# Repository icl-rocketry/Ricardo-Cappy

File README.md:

Hi. Welcome to the repo for Ricardo-Cappy.

Ricardo-Cappy is a custom HAT (Hardware Attached on Top) for the Raspberry Pi 5 to be used on the Payload lander for the 2026 ICLR launch.

It contains IMU sensors based on Ricardo-PickleRick, wirecutter modules, motor drivers for deploying landing legs, GPS and Radio capabilities as well as power systems for both the Raspberry Pi and the onboard components.

Contents:

-Hardware - contains the KiCad schematics and PCB layouts for Ricardo-Cappy, including symbols and footprints for parts not in the ICLR library. This is necessary for viewing and editing the KiCad files on your own device. 

To use the hardware files:
1. Install the ICLR symbol and footprint library (see their repo for detailed instructions, I forgot the link but you can use google)
2. Clone the repository onto your computer.
3. Install my custom libraries into KiCad (see instructions in KiCad documentation)

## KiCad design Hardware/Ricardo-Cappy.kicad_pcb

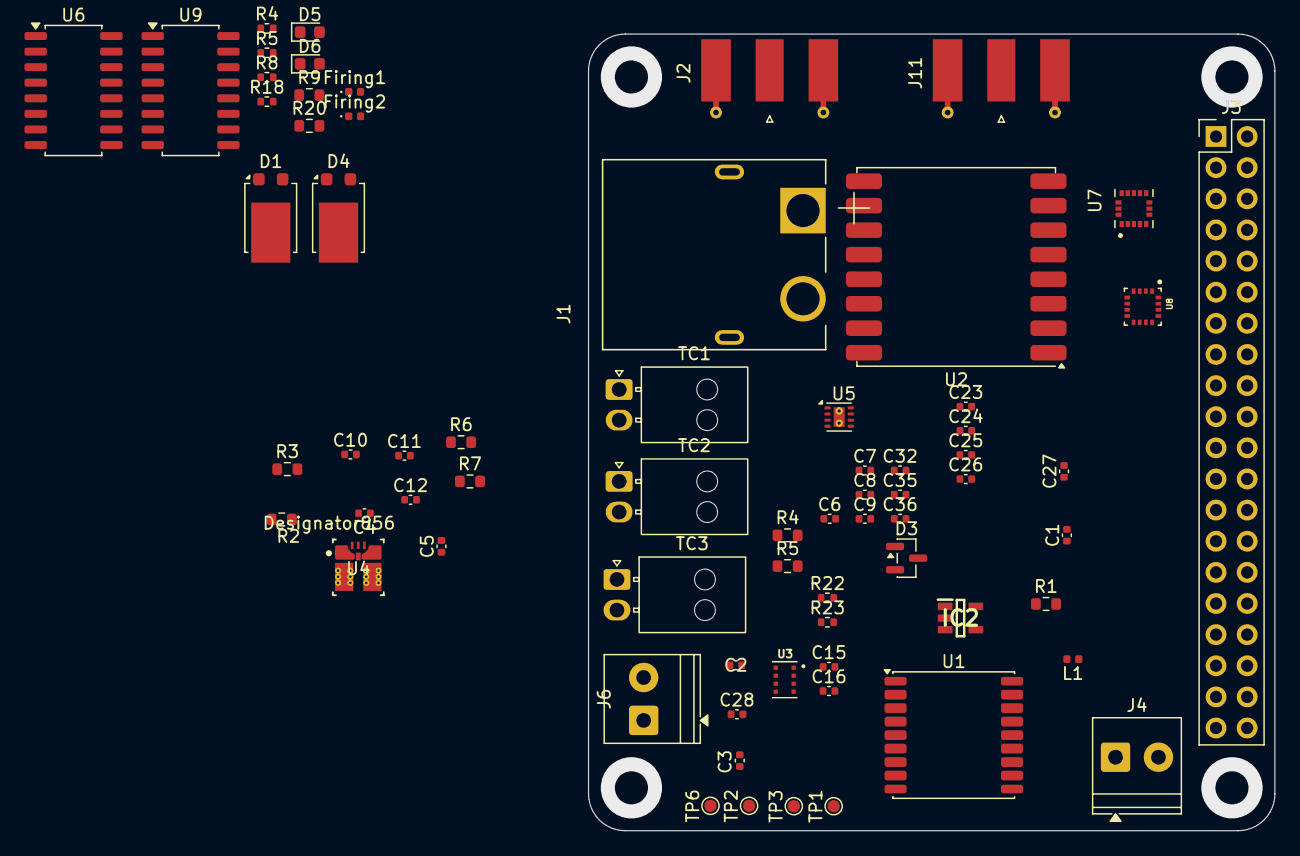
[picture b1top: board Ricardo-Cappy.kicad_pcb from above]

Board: 2 copper layers, 56.0 x 65.0 mm, 69 parts (0 on the bottom side), 47 nets, no tracks yet.

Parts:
C1, C6, C12, C24: 10nF; C_0402_1005Metric
C2, C10, C27, C35: 10uF; C_0402_1005Metric
C3, C11, C15, C16, C36: 100nF; C_0402_1005Metric
C4, C8: 10pF; C_0402_1005Metric
C5: 47uF; C_0402_1005Metric
C7: 47pF; C_0402_1005Metric
C9, C28: 1uF; C_0402_1005Metric
C23: 0.47uF; C_0402_1005Metric
C25: 0.1uF; C_0402_1005Metric
C26, C32: 2.2uF; C_0402_1005Metric
D1, D4: DST1550S; TO-277B
D3: MMBZ6V2ALT1G; SOT-23
D5, D6: RED_LED; LED_0603_1608Metric
Firing1, Firing2: EMERALD_LED; LED_0402_1005Metric
IC2: AP2205-W5-7; SOT95P282X145-5N
J1: XT60PW-M; AMASS_XT60PW-M
J2, J11: Conn_Coaxial; SMA_Molex_73251-1153_EdgeMount_Horizontal
J3: Conn_02x20_Odd_Even; PinHeader_2x20_P2.54mm_Vertical
J4, J6: Conn_01x02_Male; TerminalBlock_Phoenix_PT-1,5-2-3.5-H_1x02_P3.50mm_Horizontal
L1: 27nH; L_0402_1005Metric
R1: 10; R_0603_1608Metric
R2: 226K; R_0603_1608Metric
R3, R5: 30k; R_0603_1608Metric
R4, R8: 10K; R_0402_1005Metric
R4#2: 226k; R_0603_1608Metric
R5#2, R18: 120; R_0402_1005Metric
R6: 31.6k; R_0603_1608Metric
R7: 10k; R_0603_1608Metric
R9, R20: 120; R_0603_1608Metric
R22: 49.9k; R_0402_1005Metric
R23: 150k; R_0402_1005Metric
TC1: Motor Out; Molex_Nano-Fit_105313-xx02_1x02_P2.50mm_Horizontal
TC2: PYRO_1_OUT; Molex_Nano-Fit_105313-xx02_1x02_P2.50mm_Horizontal
TC3: PYRO_2_OUT; Molex_Nano-Fit_105313-xx02_1x02_P2.50mm_Horizontal
TP1: GPS_RESET; TestPoint_Pad_D1.0mm
TP2, TP3, TP6: TestPoint; TestPoint_Pad_D1.0mm
U1: MAX-M10S; ublox_MAX
U2: RFM95W-868S2; HOPERF_RFM9XW_SMD
U3: DPS368; XDCR_DPS310
U4: TPSM863257RDXR; RDX0007A-MFG
U5: DRV8212P; WSON-8-1EP_2x2mm_P0.5mm_EP0.9x1.6mm_ThermalVias
U6, U9: LTV-247; SOP-16_4.4x10.4mm_P1.27mm
U7: ICM-20608-G; PQFN50P300X300X80-16N
U8: MMC5983MA; PQFN50P300X300X100-16N

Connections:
+3V3: C2.1, C3.1, C15.1, C16.1, C24.1, C25.1, C26.1, C28.1, J3.1, U1.6 (V_BCKP), U1.7 (VCC_IO), U1.8 (VCC), U2.13 (3.3V), U3.6 (VDDIO), U3.8 (VDD), U5.8 (VCC), U6.10, U7.1 (VDDIO), U7.16 (VDD), U8.2 (VDD), U8.13 (VDDIO), U9.10
+5.1V: C4.1, C5.1, J3.2, J3.4, R2.1, U4.3 (VOUT), U5.1 (VM)
+5.5V: C9.1, C35.1, C36.1, IC2.1 (VIN), IC2.3 (EN)
+5V: C7.1, C8.1, C32.1, D3.1 (K), IC2.5 (VOUT), R4#2.1, R23.2
/BARO_CS: J3.22, U3.2 (~CSB)
/Cont0: J3.8, R20.1, U6.9
/Cont1: J3.28, R9.1, U9.9
/DeployPWR: C10.1, C11.1, J1.1 (+), J4.1, J6.1, R6.1, TC2.1 (+), TC3.1 (+), U4.1 (VIN)
/GPS/RXD: TP2.1 (1_1), U1.3 (RXD)
/GPS/TXD: TP6.1 (1_1), U1.2 (TXD)
/IMU1_CS: J3.16, U7.5 (CS)
/LORA_CS: J3.15, U2.5 (NSS)
/LORA_INT: J3.13, U2.14 (DIO0)
/LORA_RESET: J3.11, U2.6 (RESET)
/MAG_CS: J3.18, U8.4 (~SPI_CS)
/MOTOR_PWM1: J3.32, U5.6 (IN1)
/MOTOR_PWM2: J3.33, U5.5 (IN2)
/Nuke 0: Firing1.2 (A), J3.36, R4.1
/Nuke 1: Firing2.2 (A), J3.10, R8.1
/PI_MISO: J3.21, U2.2 (MISO), U7.4 (AD0/SDO), U8.5 (SPI_SDO)
/PI_MISO_1: J3.35, U3.5 (SDO)
/PI_MOSI: J3.19, U2.3 (MOSI), U7.3 (SDA/SDI), U8.16 (SDA/SPI_SDI)
/PI_MOSI_1: J3.38, U3.3 (SDI)
/PI_SCLK: J3.23, U2.4 (SCK), U7.2 (SCL/SCLK), U8.1 (SCL/SPI_SCK)
/PI_SCLK_1: J3.40, U3.4 (SCK)
/PPS: J3.31, TP3.1 (1_1), U1.4 (TIMEPULSE)
/SCL: J3.5, U1.17 (SCL)
/SDA: J3.3, U1.16 (SDA)
GND: C1.2, C2.2, C3.2, C5.2, C6.2, C7.2, C9.2, C10.2, C11.2, C12.2, C15.2, C16.2, C23.2, C24.2, C25.2, C26.2, C27.2, C28.2, C32.2, C35.2, C36.2, D3.3 (A), D5.1 (K), D6.1 (K), IC2.2 (GND), J1.2 (-), J2.2 (Ext), J3.6, J3.9, J3.14, J3.20, J3.25, J3.30, J3.34, J3.39, J11.2 (Ext), R3.2, R4.2, R5.2, R5#2.2, R7.2, R8.2, R18.2, R22.1, U1.1 (GND), U1.10 (GND), U1.12 (GND), U2.1 (GND), U2.8 (GND), U2.10 (GND), U3.1 (GND), U3.7 (GND), U4.4 (PGND), U5.4 (GND), U5.9 (GND), U7.8 (FSYNC), U7.9 (GND), U7.10 (GND), U7.11 (GND), U7.12 (GND), U7.13 (GND), U7.15 (GND), U8.9 (GND), U8.11 (GND)
unnamed: C1.1, L1.1, R1.1
unnamed: D4.1 (A), D4.2 (A), J6.2, TC3.2 (-), U9.7
unnamed: D5.2 (A), R20.2
unnamed: D6.2 (A), R9.2
unnamed: D1.1 (A), D1.2 (A), J4.2, TC2.2 (-), U6.7
unnamed: Firing1.1 (K), R18.1
unnamed: Firing2.1 (K), R5#2.1
unnamed: IC2.4 (ADJ/NC), R22.2, R23.1
unnamed: J2.1 (In), L1.2, U1.11 (RF_IN)
unnamed: J11.1 (In), U2.9 (ANT)
unnamed: TC1.1 (+), U5.3 (OUT2)
unnamed: TC1.2 (-), U5.2 (OUT1)
unnamed: R1.2, U1.14 (VCC_RF)
unnamed: TP1.1 (1_1), U1.9 (~RESET)
unnamed: C6.1, C12.1, R6.2, R7.1, U4.6 (EN)
unnamed: C4.2, C8.2, R2.2, R3.1, R4#2.2, R5.1, U4.7 (FB)
unnamed: C23.1, U7.14 (REGOUT)
unnamed: C27.1, U8.10 (CAP)

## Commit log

2026-03-21 Reorganised
2026-03-21 Relabelled some of the files
2026-03-21 Renamed some files
2026-03-21 Modified power
2026-03-21 Fixed power
2026-06-02 Added README.md
2026-06-02 Enhance hardware section with usage instructions
    Expanded the hardware section to include details on symbols and footprints, and added instructions for using the hardware files.
2026-06-09 Corrected accidentally deleted connection, reorganised PCB layout (still very WIP)
